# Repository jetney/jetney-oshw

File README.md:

# oshw
Open-source hardware design files from Jetney Development.

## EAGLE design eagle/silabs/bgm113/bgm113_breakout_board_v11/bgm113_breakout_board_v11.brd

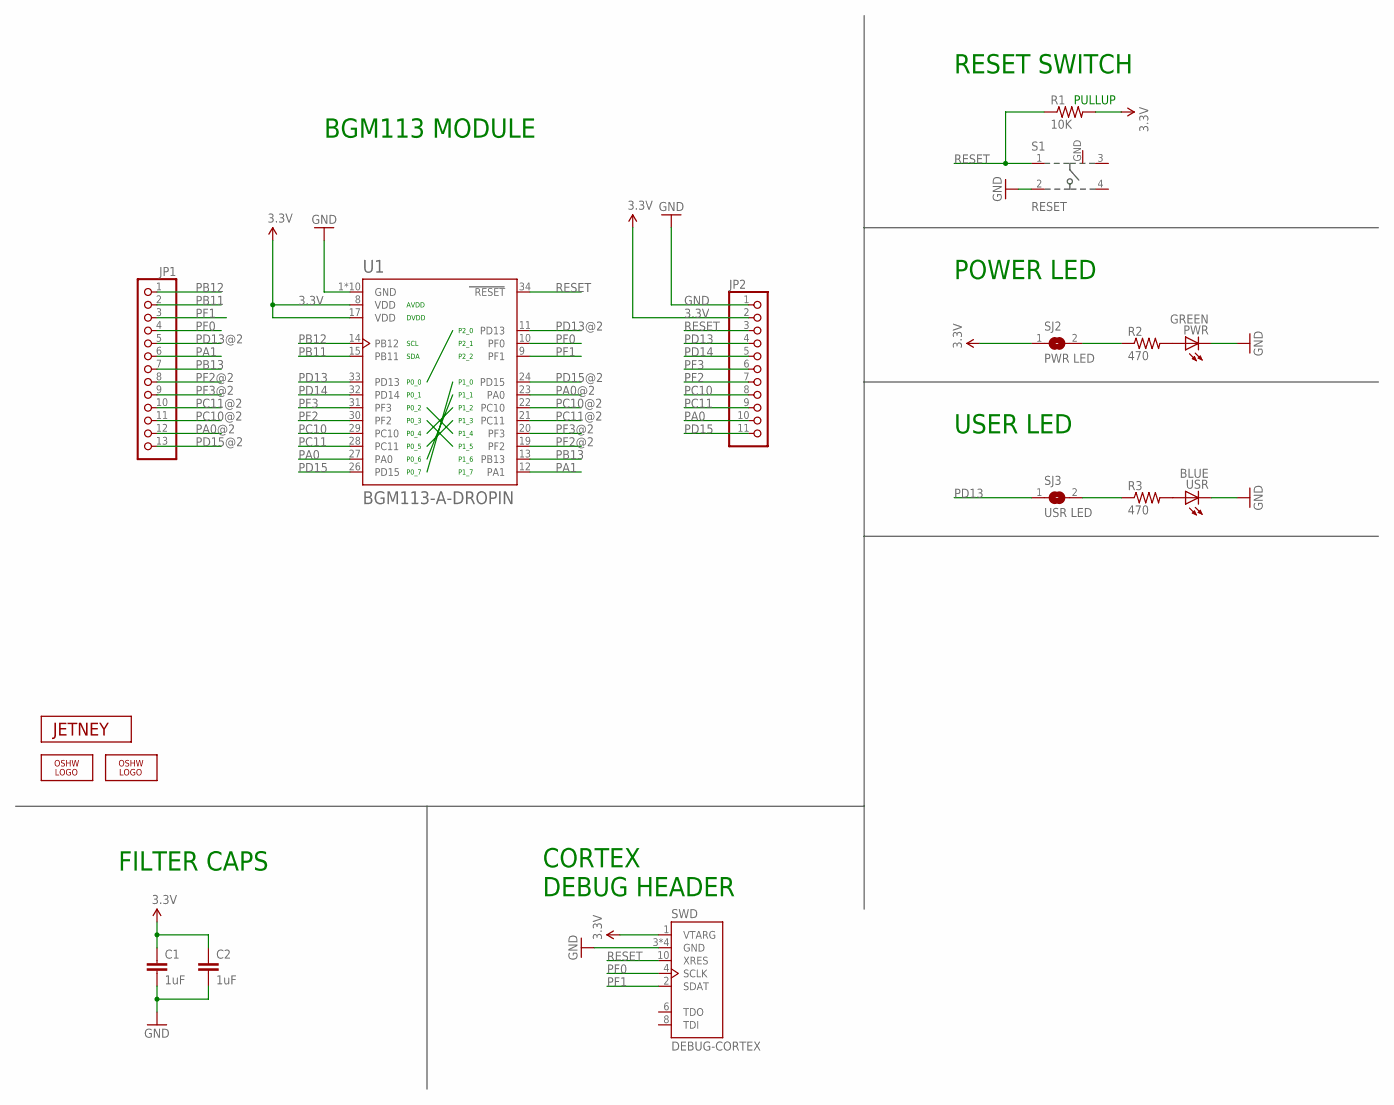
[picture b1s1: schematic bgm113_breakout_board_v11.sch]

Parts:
C1, C2: 1uF; 0603-CAP
JP1: PINHD-1X13; 1X13
JP2: PINHD-1X11; 1X11
LOGO1: OSHW_LOGO_FILLX0100-NT; OSHW_FILLX100_NOTEXT
LOGO2: OSHW_LOGO_FILLX0070-NT; OSHW_FILLX70_NOTEXT
PWR: GREEN; CHIPLED_0805
R1: 10K; 0603-RES
R2, R3: 470; R0603
S1: RESET; 101-IG
SJ2: PWR LED; SJ
SJ3: USR LED; SJ
SWD: DEBUG-CORTEX; DEBUG-50MIL
U1: BGM113-A-DROPIN; BLE113-A
U$2: JETNEY-LOGO-12
USR: BLUE; CHIPLED_0805

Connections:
3.3V: C1.1, C2.1, JP2.2, R1.2, SJ2.1, SWD.1 (VTARG), U1.8 (VDD), U1.17 (VDD)
GND: C1.2, C2.2, JP2.1, PWR.C, S1.2, S1.GND, SWD.3 (GND), SWD.5 (GND), SWD.7 (GND), SWD.9 (GND), U1.1 (GND), U1.2 (GND), U1.3 (GND), U1.4 (GND), U1.5 (GND), U1.6 (GND), U1.7 (GND), U1.18 (GND), U1.25 (GND), U1.36 (GND), USR.C
unnamed: PWR.A, R2.2
unnamed: R2.1, SJ2.2
unnamed: R3.2, USR.A
unnamed: R3.1, SJ3.2
PA0: JP2.10, U1.27 (PA0)
PA0@2: JP1.12, U1.23 (PA0)
PA1: JP1.6, U1.12 (PA1)
PB11: JP1.2, U1.15 (PB11)
PB12: JP1.1, U1.14 (PB12)
PB13: JP1.7, U1.13 (PB13)
PC10: JP2.8, U1.29 (PC10)
PC10@2: JP1.11, U1.22 (PC10)
PC11: JP2.9, U1.28 (PC11)
PC11@2: JP1.10, U1.21 (PC11)
PD13: JP2.4, SJ3.1, U1.33 (PD13)
PD13@2: JP1.5, U1.11 (PD13)
PD14: JP2.5, U1.32 (PD14)
PD15: JP2.11, U1.26 (PD15)
PD15@2: JP1.13, U1.24 (PD15)
PF0: JP1.4, SWD.4 (SCLK), U1.10 (PF0)
PF1: JP1.3, SWD.2 (SDAT), U1.9 (PF1)
PF2: JP2.7, U1.30 (PF2)
PF2@2: JP1.8, U1.19 (PF2)
PF3: JP2.6, U1.31 (PF3)
PF3@2: JP1.9, U1.20 (PF3)
RESET: JP2.3, R1.1, S1.1, SWD.10 (XRES), U1.34 (RESET)

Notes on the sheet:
POWER LED
USER LED
CORTEX DEBUG HEADER
BGM113 MODULE
RESET SWITCH
PULLUP
FILTER CAPS

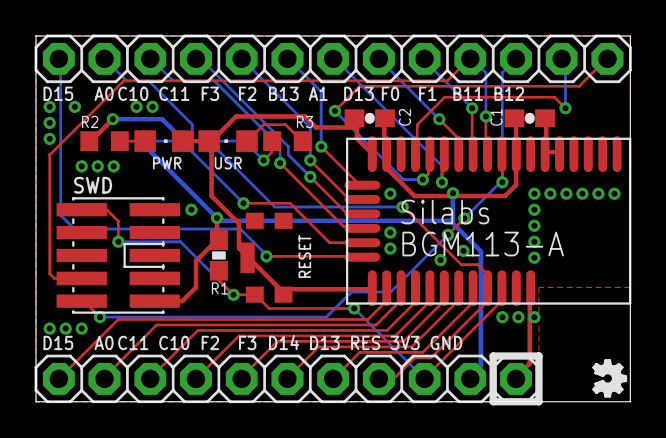
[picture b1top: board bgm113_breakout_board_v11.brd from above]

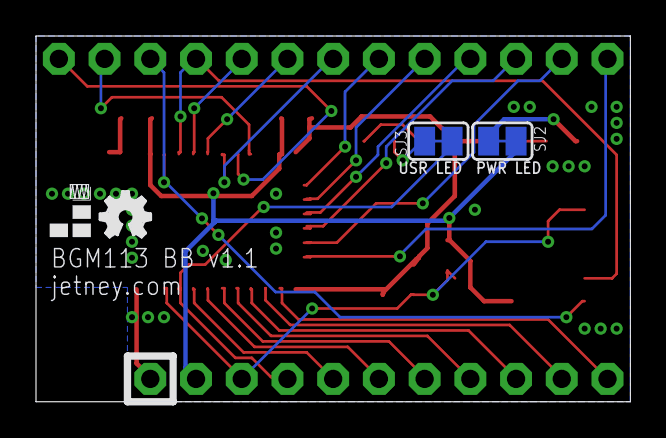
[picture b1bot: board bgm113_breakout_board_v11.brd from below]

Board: 2 copper layers, 33.0 x 20.3 mm, 17 parts (4 on the bottom side), 28 nets.

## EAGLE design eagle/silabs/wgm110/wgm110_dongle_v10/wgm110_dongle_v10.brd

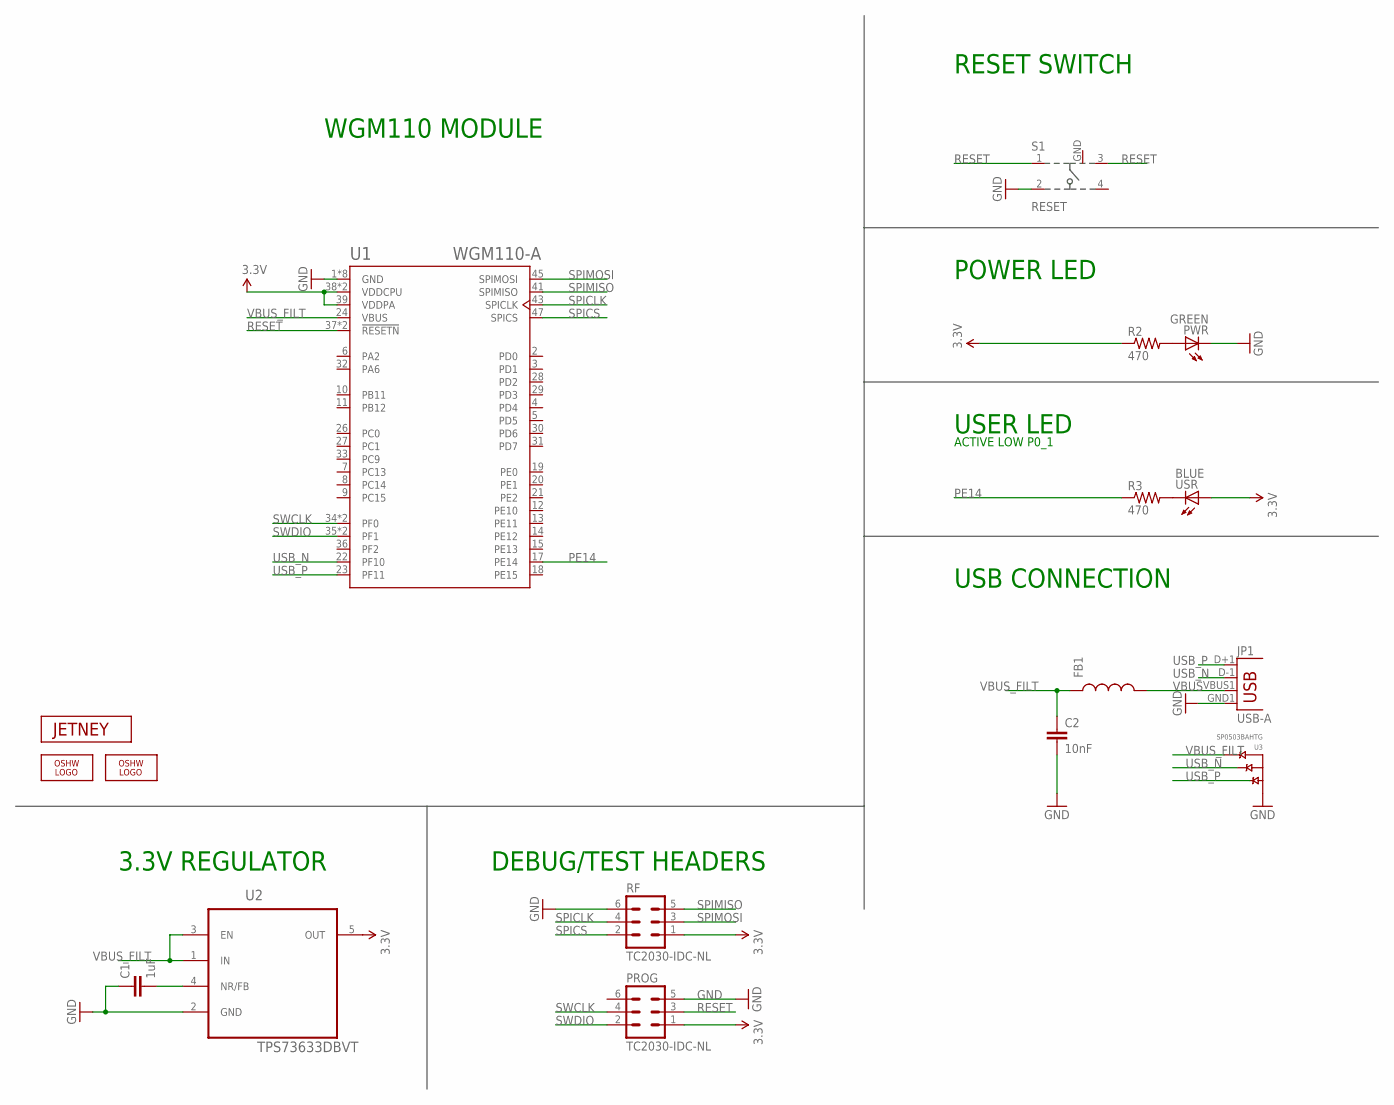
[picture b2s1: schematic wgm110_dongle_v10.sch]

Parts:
C1: 1uF; 0603-CAP
C2: 10nF; 0603-CAP
FB1: INDUCTOR0805; 0805
JP1: USB-A; USB-A-SMT-MALE-MOLEX
LOGO1: OSHW_LOGO_FILLX0100-NT; OSHW_FILLX100_NOTEXT
LOGO2: OSHW_LOGO_FILLX0070-NT; OSHW_FILLX70_NOTEXT
PROG: TC2030-IDC-NL
PWR: GREEN; CHIPLED_0805
R2, R3: 470; R0603
RF: TC2030-IDC-NL
S1: RESET; 101-IG
U1: WGM110-A
U2: TPS73633DBVT; SOT95P280X145-5N
U3: SP0503BAHTG; SOT143
U$2: JETNEY-LOGO-12
USR: BLUE; CHIPLED_0805

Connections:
3.3V: PROG.1, R2.1, RF.1, U1.38 (VDDCPU), U1.39 (VDDPA), U1.51 (VDDCPU), U2.5 (OUT), USR.A
GND: C1.1, C2.2, JP1.GND1 (GND), PROG.5, PWR.C, RF.6, S1.2, S1.GND, U1.1 (GND), U1.16 (GND), U1.25 (GND), U1.40 (GND), U1.42 (GND), U1.44 (GND), U1.46 (GND), U1.48 (GND), U2.2 (GND), U3.1 (GND)
PE14: R3.1, U1.17 (PE14)
PE14_LED: R3.2, USR.C
PWR_LED: PWR.A, R2.2
REG_BP: C1.2, U2.4 (NR/FB)
RESET: PROG.3, S1.1, S1.3, U1.37 (!RESETN), U1.49 (!RESETN)
SPICLK: RF.4, U1.43 (SPICLK)
SPICS: RF.2, U1.47 (SPICS)
SPIMISO: RF.5, U1.41 (SPIMISO)
SPIMOSI: RF.3, U1.45 (SPIMOSI)
SWCLK: PROG.4, U1.34 (PF0), U1.50 (PF0)
SWDIO: PROG.2, U1.35 (PF1), U1.52 (PF1)
USB_N: JP1.D-1 (D-), U1.22 (PF10), U3.3 (B)
USB_P: JP1.D+1 (D+), U1.23 (PF11), U3.2 (A)
VBUS: FB1.2, JP1.VBUS1 (VBUS)
VBUS_FILT: C2.1, FB1.1, U1.24 (VBUS), U2.1 (IN), U2.3 (EN), U3.4 (C)

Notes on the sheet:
POWER LED
USER LED
DEBUG/TEST HEADERS
WGM110 MODULE
RESET SWITCH
3.3V REGULATOR
ACTIVE LOW P0_1
USB CONNECTION

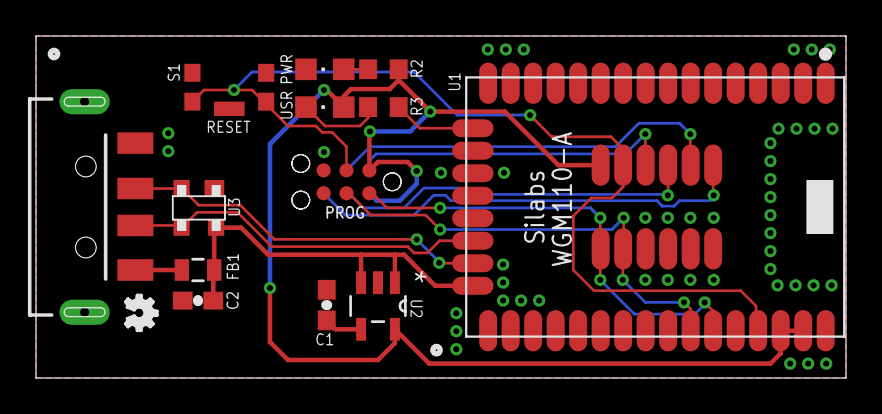
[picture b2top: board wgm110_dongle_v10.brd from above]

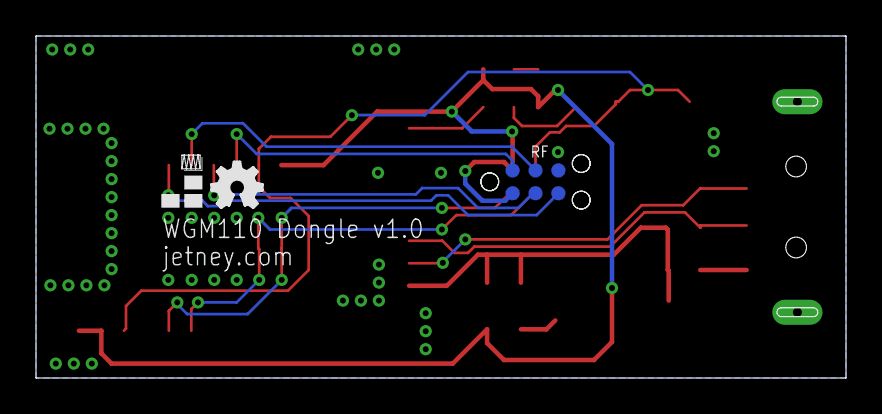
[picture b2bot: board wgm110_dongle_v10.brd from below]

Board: 2 copper layers, 45.0 x 19.0 mm, 17 parts (3 on the bottom side), 17 nets.

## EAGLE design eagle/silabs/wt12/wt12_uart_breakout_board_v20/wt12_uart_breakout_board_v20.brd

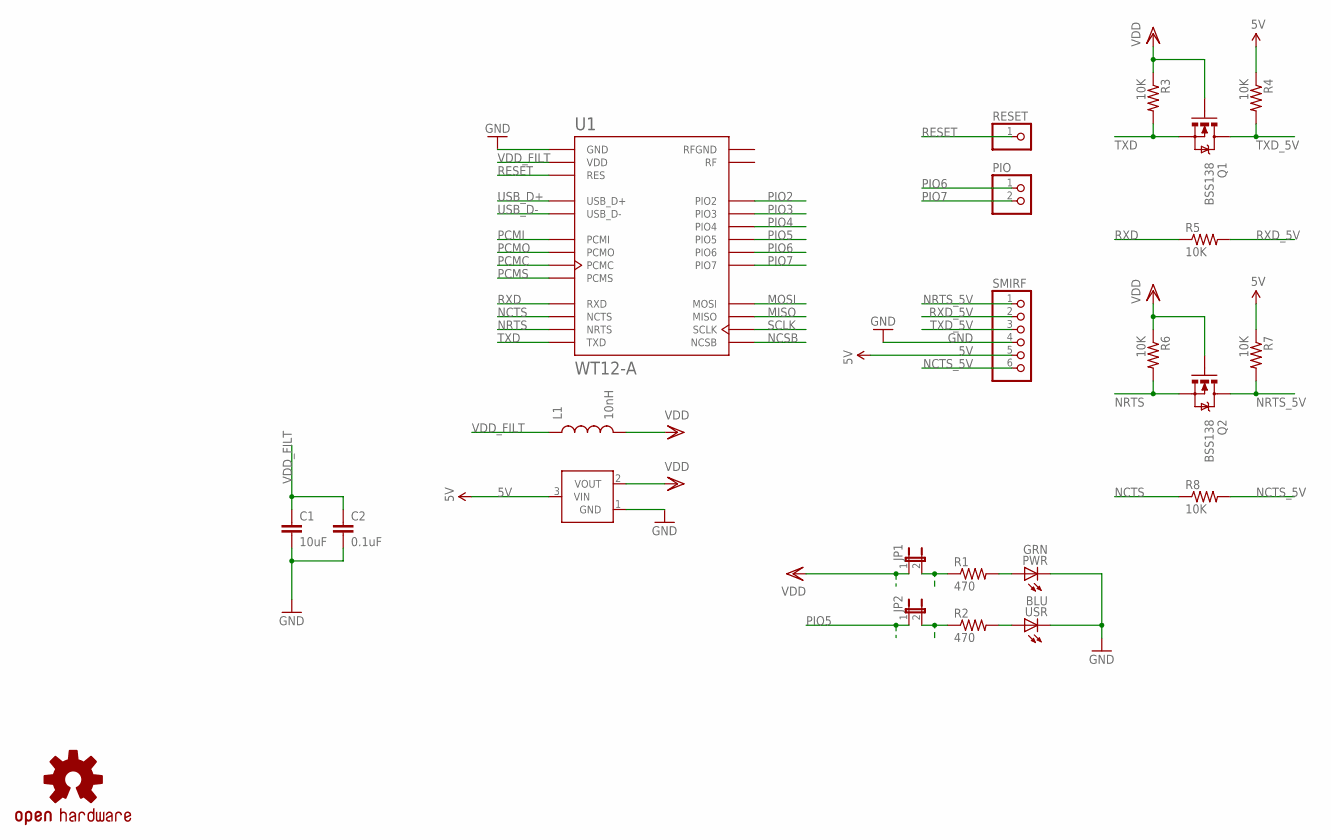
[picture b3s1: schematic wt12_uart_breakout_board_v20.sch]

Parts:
C1: 10uF; 0603-CAP
C2: 0.1uF; 0603-CAP
JP1, JP2: JUMPER-2SMD-NC; SJ_2S
L1: 10nH; 0603
PIO: PINHD-1X2; 1X02
PWR: GRN; CHIPLED_0805
Q1, Q2: BSS138; SOT23-3
R1, R2: 470; 0603-RES
R3, R4, R5, R6, R7, R8: 10K; 0603-RES
RESET: PINHD-1X1; 1X01
SMIRF: PINHD-1X6; 1X06
U1: WT12-A
U2: MCP1700; SOT23-3
U$5: OSHW-LOGOM; OSHW-LOGO-M
USR: BLU; CHIPLED_0805

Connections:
5V: R4.1, R7.1, SMIRF.5, U2.3 (VIN)
GND: C1.2, C2.2, PWR.C, SMIRF.4, U1.GND, U1.GND@2 (GND), U1.GND@3 (GND), U1.GND@4 (GND), U2.1 (GND), USR.C
MISO: U1.MISO
MOSI: U1.MOSI
unnamed: PWR.A, R1.2
unnamed: R2.2, USR.A
unnamed: JP2.2, R2.1
NCSB: U1.NCSB
NCTS: R8.1, U1.NCTS
NCTS_5V: R8.2, SMIRF.6
NRTS: Q2.2 (S), R6.2, U1.NRTS
NRTS_5V: Q2.3 (D), R7.2, SMIRF.1
PCMC: U1.PCMC
PCMI: U1.PCMI
PCMO: U1.PCMO
PCMS: U1.PCMS
PIO2: U1.PIO2
PIO3: U1.PIO3
PIO4: U1.PIO4
PIO5: JP2.1, U1.PIO5
PIO6: PIO.1, U1.PIO6
PIO7: PIO.2, U1.PIO7
RESET: RESET.1, U1.RES
RXD: R5.1, U1.RXD
RXD_5V: R5.2, SMIRF.2
SCLK: U1.SCLK
TXD: Q1.2 (S), R3.2, U1.TXD
TXD_5V: Q1.3 (D), R4.2, SMIRF.3
USB_D+: U1.USB_D+
USB_D-: U1.USB_D-
VDD: JP1.1, L1.2, Q1.1 (G), Q2.1 (G), R3.1, R6.1, U2.2 (VOUT)
VDDJP1: JP1.2, R1.1
VDD_FILT: C1.1, C2.1, L1.1, U1.VDD, U1.VDD@2 (VDD)

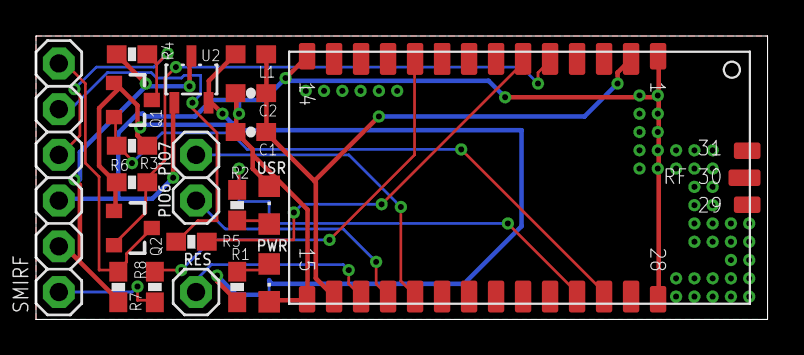
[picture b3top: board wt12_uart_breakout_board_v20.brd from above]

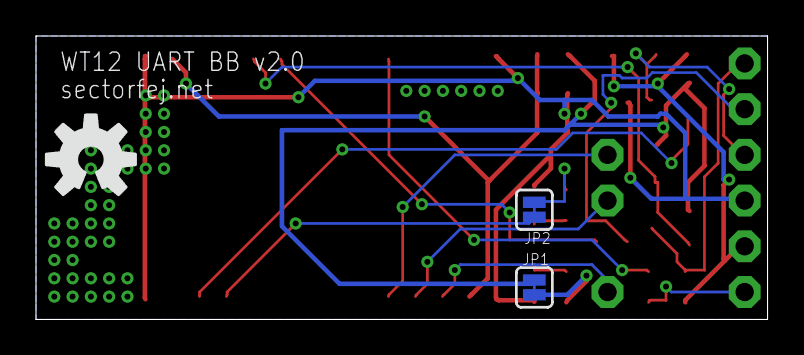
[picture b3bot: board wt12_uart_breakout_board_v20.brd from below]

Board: 2 copper layers, 40.6 x 15.7 mm, 23 parts (3 on the bottom side), 20 nets.

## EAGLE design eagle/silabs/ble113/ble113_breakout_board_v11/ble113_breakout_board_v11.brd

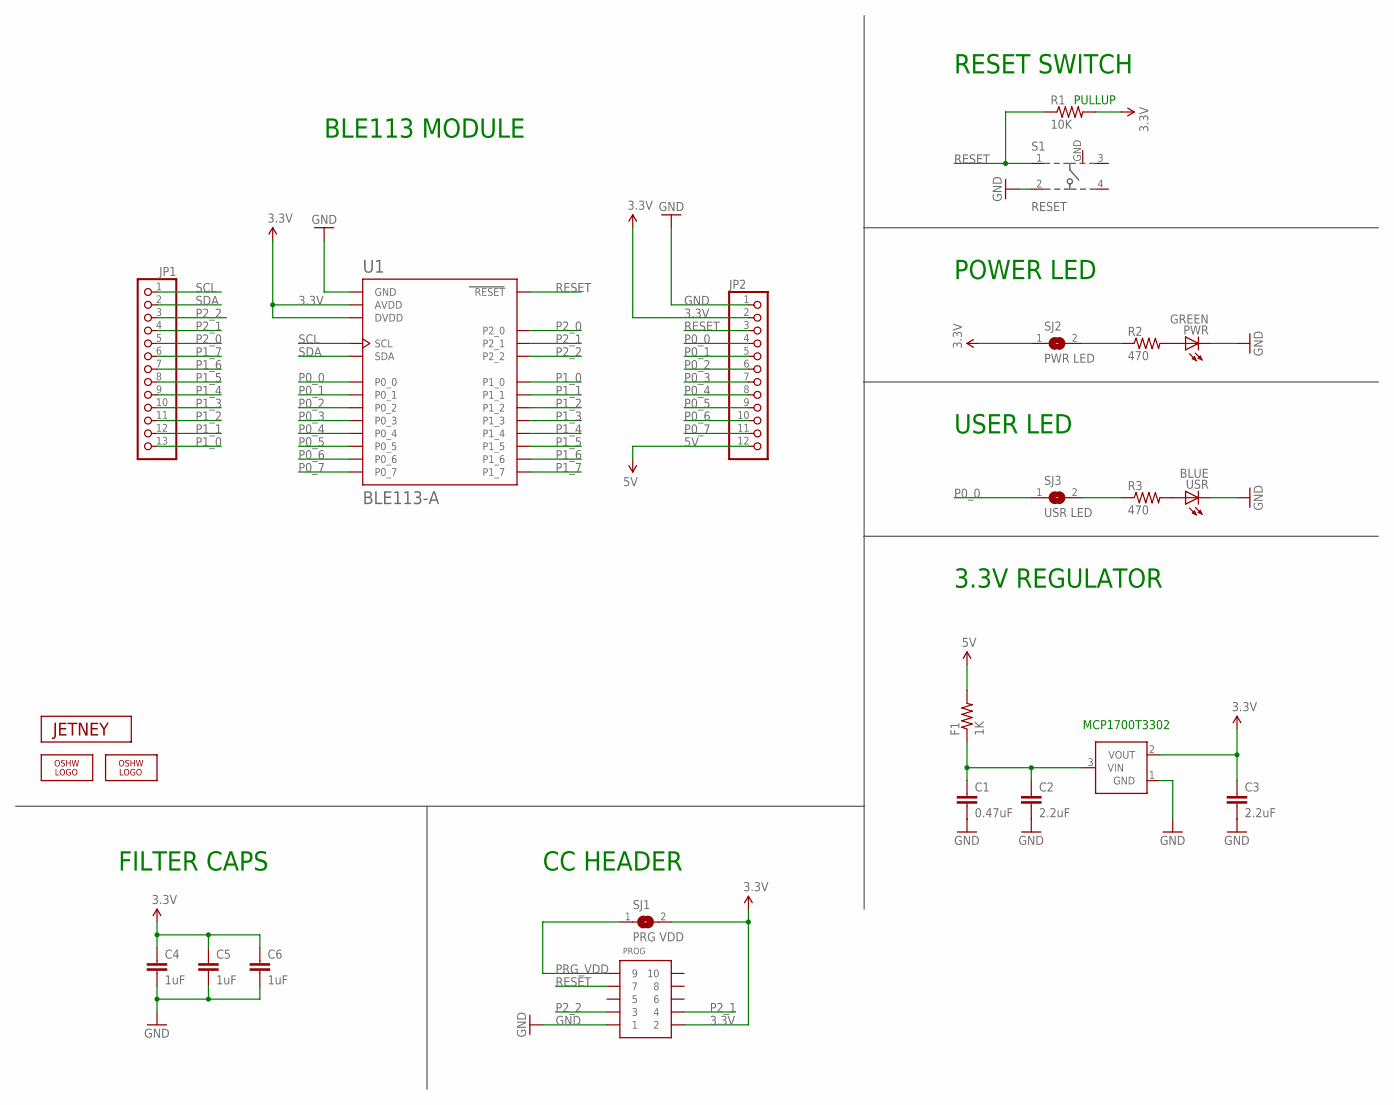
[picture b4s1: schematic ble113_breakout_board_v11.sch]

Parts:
C1: 0.47uF; 0603-CAP
C2, C3: 2.2uF; 0603-CAP
C4, C5, C6: 1uF; 0603-CAP
F1: 1K; 0805
JP1: PINHD-1X13; 1X13
JP2: PINHD-1X12; 1X12
LOGO1: OSHW_LOGO_FILLX0100-NT; OSHW_FILLX100_NOTEXT
LOGO2: OSHW_LOGO_FILLX0070-NT; OSHW_FILLX70_NOTEXT
PROG: CONN_5-2-FTSH-V; FTSH-105-DV
PWR: GREEN; CHIPLED_0805
R1: 10K; 0603-RES
R2, R3: 470; R0603
S1: RESET; 101-IG
SJ1: PRG VDD; SJ
SJ2: PWR LED; SJ
SJ3: USR LED; SJ
U1: BLE113-A
U2: MCP1700; SOT23-3
U$2: JETNEY-LOGO-12
USR: BLUE; CHIPLED_0805

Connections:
3.3V: C3.1, C4.1, C5.1, C6.1, JP2.2, PROG.2, R1.2, SJ1.2, SJ2.1, U1.AVDD, U1.DVDD, U2.2 (VOUT)
5V: F1.2, JP2.12
5VF: C1.1, C2.1, F1.1, U2.3 (VIN)
GND: C1.2, C2.2, C3.2, C4.2, C5.2, C6.2, JP2.1, PROG.1, PWR.C, S1.2, S1.GND, U1.GND, U1.GND@2 (GND), U1.GND@3 (GND), U1.GND@4 (GND), U1.GND@5 (GND), U1.GND@6 (GND), U1.GND@7 (GND), U1.GND@8 (GND), U1.GND@9 (GND), U1.GND@10 (GND), U2.1 (GND), USR.C
unnamed: PWR.A, R2.2
unnamed: R2.1, SJ2.2
unnamed: R3.2, USR.A
unnamed: R3.1, SJ3.2
P0_0: JP2.4, SJ3.1, U1.P0_0
P0_1: JP2.5, U1.P0_1
P0_2: JP2.6, U1.P0_2
P0_3: JP2.7, U1.P0_3
P0_4: JP2.8, U1.P0_4
P0_5: JP2.9, U1.P0_5
P0_6: JP2.10, U1.P0_6
P0_7: JP2.11, U1.P0_7
P1_0: JP1.13, U1.P1_0
P1_1: JP1.12, U1.P1_1
P1_2: JP1.11, U1.P1_2
P1_3: JP1.10, U1.P1_3
P1_4: JP1.9, U1.P1_4
P1_5: JP1.8, U1.P1_5
P1_6: JP1.7, U1.P1_6
P1_7: JP1.6, U1.P1_7
P2_0: JP1.5, U1.P2_0
P2_1: JP1.4, PROG.4, U1.P2_1
P2_2: JP1.3, PROG.3, U1.P2_2
PRG_VDD: PROG.9, SJ1.1
RESET: JP2.3, PROG.7, R1.1, S1.1, U1.RESET
SCL: JP1.1, U1.SCL
SDA: JP1.2, U1.SDA

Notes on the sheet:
POWER LED
USER LED
CC HEADER
BLE113 MODULE
3.3V REGULATOR
RESET SWITCH
PULLUP
MCP1700T3302
FILTER CAPS

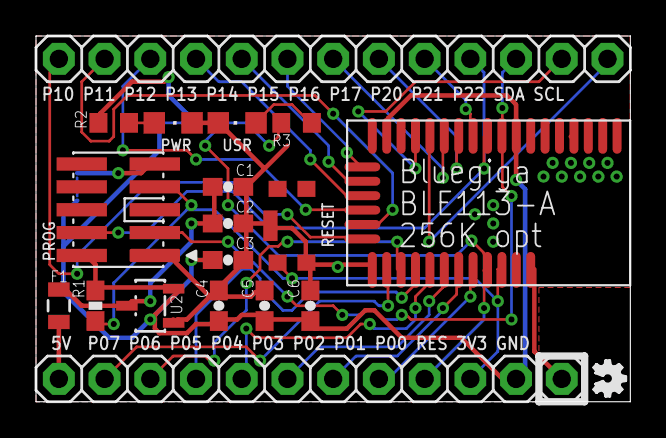
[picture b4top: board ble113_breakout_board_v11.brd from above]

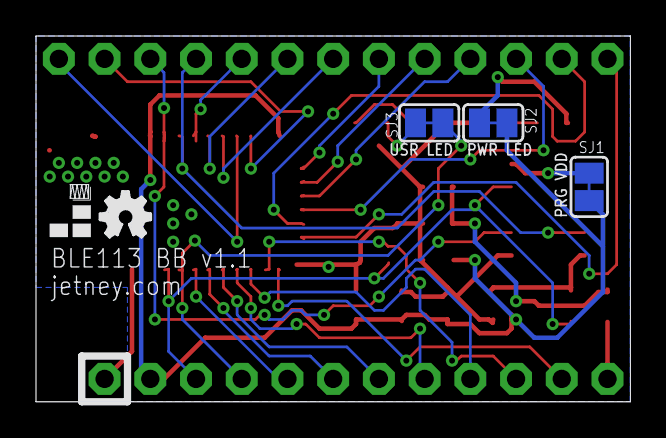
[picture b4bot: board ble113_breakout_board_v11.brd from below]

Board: 2 copper layers, 33.0 x 20.3 mm, 24 parts (5 on the bottom side), 31 nets.

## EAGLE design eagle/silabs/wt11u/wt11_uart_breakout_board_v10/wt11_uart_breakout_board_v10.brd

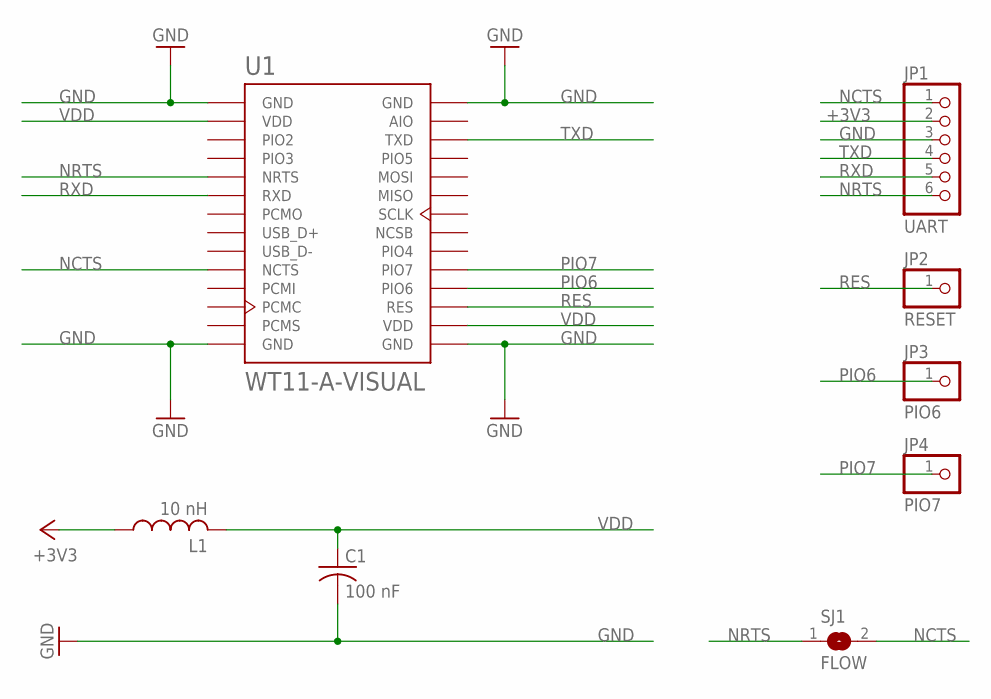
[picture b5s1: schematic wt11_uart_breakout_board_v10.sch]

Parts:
C1: 100 nF; C0603K
JP1: UART; 1X06
JP2: RESET; 1X01
JP3: PIO6; 1X01
JP4: PIO7; 1X01
L1: 10 nH; L2012C
SJ1: FLOW; SJ
U1: WT11-A-VISUAL; WT11-A

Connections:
+3V3: JP1.2, L1.1
GND: C1.2, JP1.3, U1.GND1 (GND), U1.GND2 (GND), U1.GND3 (GND), U1.GND4 (GND)
NCTS: JP1.1, SJ1.2, U1.NCTS
NRTS: JP1.6, SJ1.1, U1.NRTS
PIO6: JP3.1, U1.PIO6
PIO7: JP4.1, U1.PIO7
RES: JP2.1, U1.RES
RXD: JP1.5, U1.RXD
TXD: JP1.4, U1.TXD
VDD: C1.1, L1.2, U1.VDD1 (VDD), U1.VDD2 (VDD)

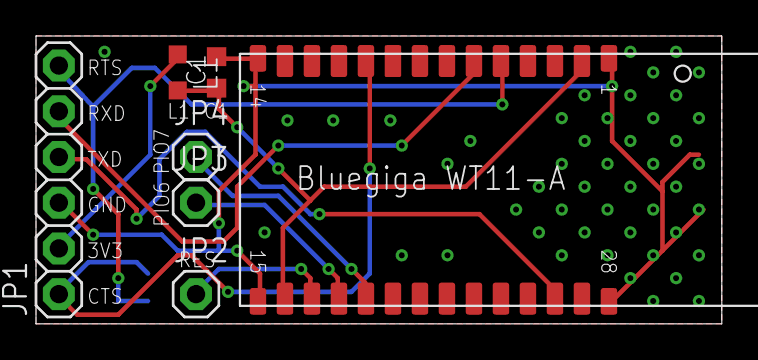
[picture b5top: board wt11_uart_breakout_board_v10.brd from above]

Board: 2 copper layers, 38.1 x 16.0 mm, 8 parts (1 on the bottom side), 10 nets.

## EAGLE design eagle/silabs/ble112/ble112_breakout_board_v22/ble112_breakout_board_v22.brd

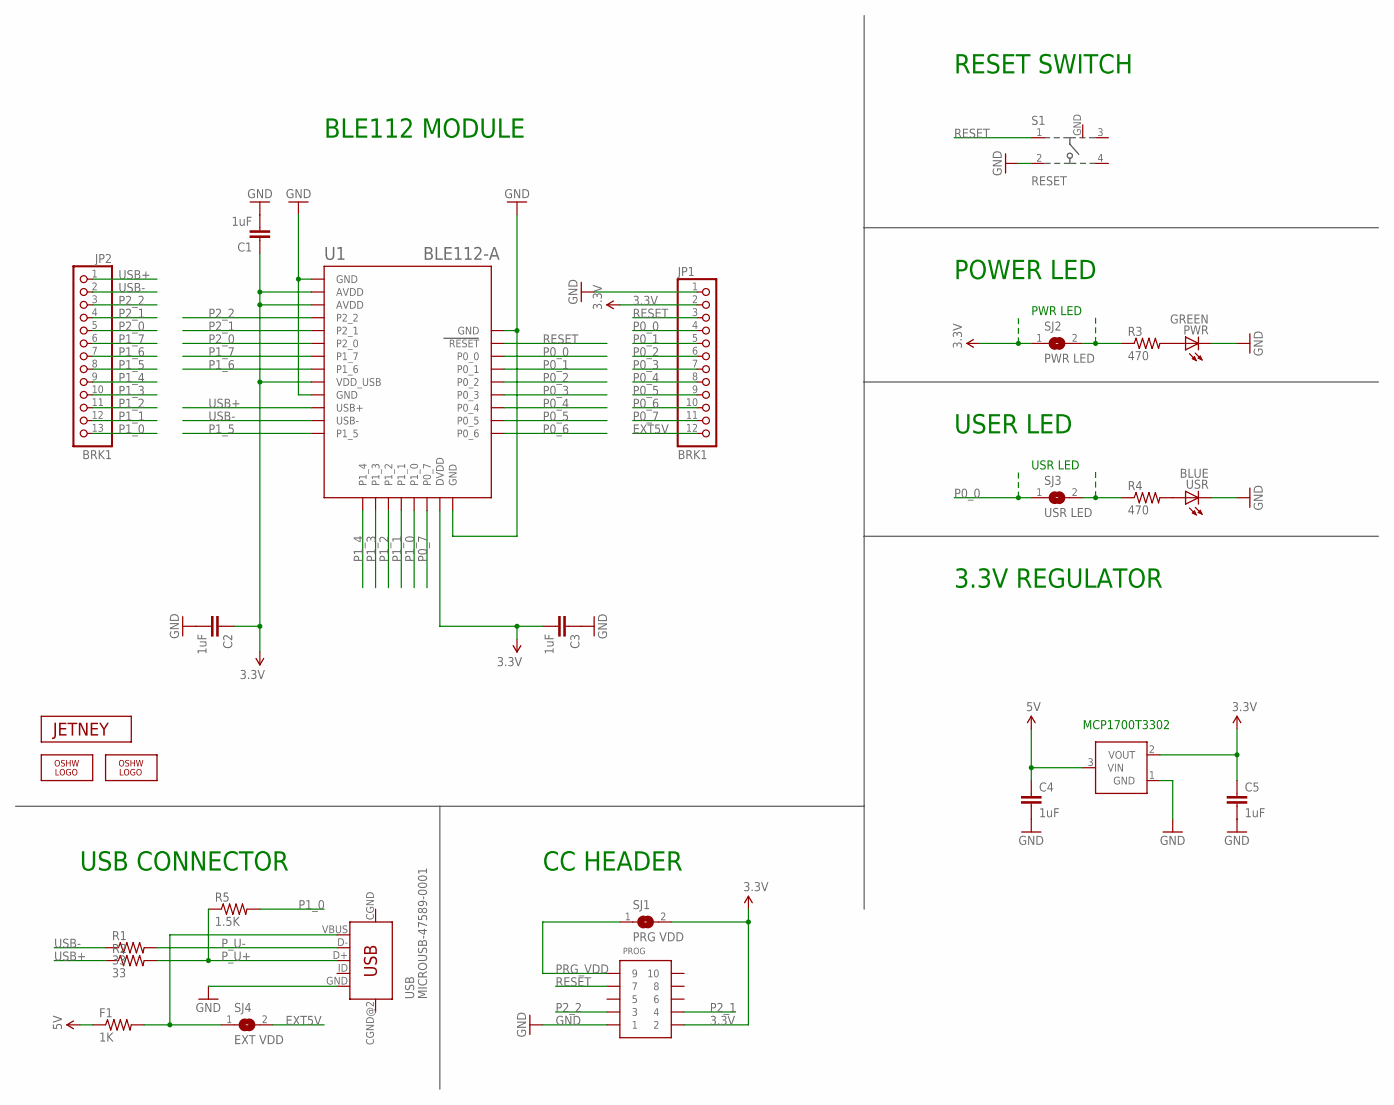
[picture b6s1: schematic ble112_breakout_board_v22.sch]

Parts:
C1, C2, C3, C4, C5: 1uF; 0603-CAP
F1: 1K; 0805
JP1: BRK1; 1X12
JP2: BRK1; 1X13
LOGO1, LOGO2: OSHW_LOGO_FILLX0100-NT; OSHW_FILLX100_NOTEXT
PROG: CONN_5-2-FTSH-V; FTSH-105-DV
PWR: GREEN; CHIPLED_0805
R1, R2: 33; 0603-RES
R3, R4: 470; R0603
R5: 1.5K; 0603-RES
S1: RESET; 101-IG
SJ1: PRG VDD; SJ
SJ2: PWR LED; SJ
SJ3: USR LED; SJ
SJ4: EXT VDD; SJ
U1: BLE112-A
U2: MCP1700; SOT23-3
U$3: JETNEY-LOGO-12
USB: MICROUSB-47589-0001
USR: BLUE; CHIPLED_0805

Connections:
3.3V: C1.1, C2.1, C3.2, C5.1, JP1.2, PROG.2, SJ1.2, SJ2.1, U1.AVDD, U1.AVDD@2 (AVDD), U1.DVDD, U1.VDD_USB, U2.2 (VOUT)
5V: C4.1, F1.1, U2.3 (VIN)
EXT5V: JP1.12, SJ4.2
GND: C1.2, C2.2, C3.1, C4.2, C5.2, JP1.1, PROG.1, PWR.C, S1.2, S1.GND, U1.GND, U1.GND@2 (GND), U1.GND@3 (GND), U1.GND@4 (GND), U2.1 (GND), USB.GND, USR.C
unnamed: PWR.A, R3.2
unnamed: R3.1, SJ2.2
unnamed: R4.2, USR.A
unnamed: R4.1, SJ3.2
P0_0: JP1.4, SJ3.1, U1.P0_0
P0_1: JP1.5, U1.P0_1
P0_2: JP1.6, U1.P0_2
P0_3: JP1.7, U1.P0_3
P0_4: JP1.8, U1.P0_4
P0_5: JP1.9, U1.P0_5
P0_6: JP1.10, U1.P0_6
P0_7: JP1.11, U1.P0_7
P1_0: JP2.13, R5.2, U1.P1_0
P1_1: JP2.12, U1.P1_1
P1_2: JP2.11, U1.P1_2
P1_3: JP2.10, U1.P1_3
P1_4: JP2.9, U1.P1_4
P1_5: JP2.8, U1.P1_5
P1_6: JP2.7, U1.P1_6
P1_7: JP2.6, U1.P1_7
P2_0: JP2.5, U1.P2_0
P2_1: JP2.4, PROG.4, U1.P2_1
P2_2: JP2.3, PROG.3, U1.P2_2
PRG_VDD: PROG.9, SJ1.1
P_U+: R2.2, R5.1, USB.D+
P_U-: R1.2, USB.D-
RESET: JP1.3, PROG.7, S1.1, U1.RESET
USB+: JP2.1, R2.1, U1.USB+
USB-: JP2.2, R1.1, U1.USB-
VBUS: F1.2, SJ4.1, USB.VBUS

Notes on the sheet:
PWR LED
USR LED
POWER LED
USER LED
USB CONNECTOR
CC HEADER
BLE112 MODULE
3.3V REGULATOR
RESET SWITCH
MCP1700T3302

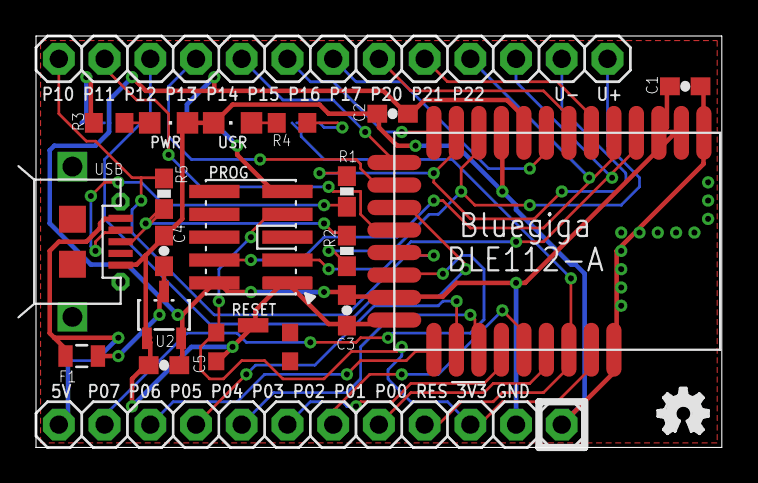
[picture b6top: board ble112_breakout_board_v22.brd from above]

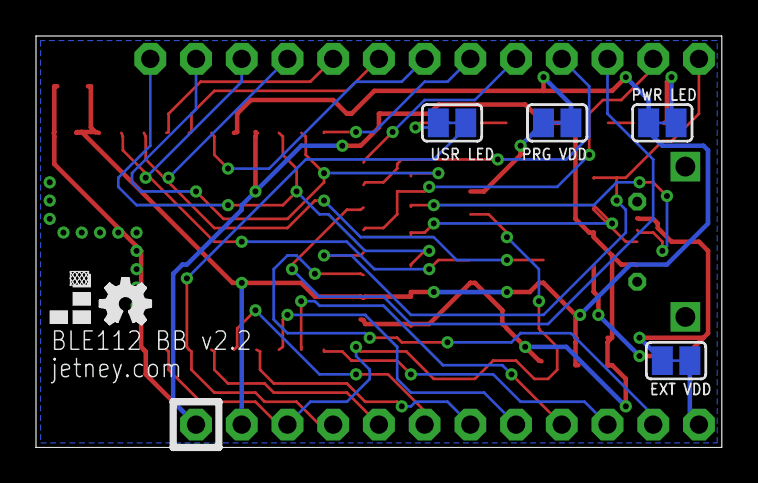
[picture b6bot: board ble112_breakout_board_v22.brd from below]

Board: 2 copper layers, 38.1 x 22.9 mm, 27 parts (6 on the bottom side), 34 nets.

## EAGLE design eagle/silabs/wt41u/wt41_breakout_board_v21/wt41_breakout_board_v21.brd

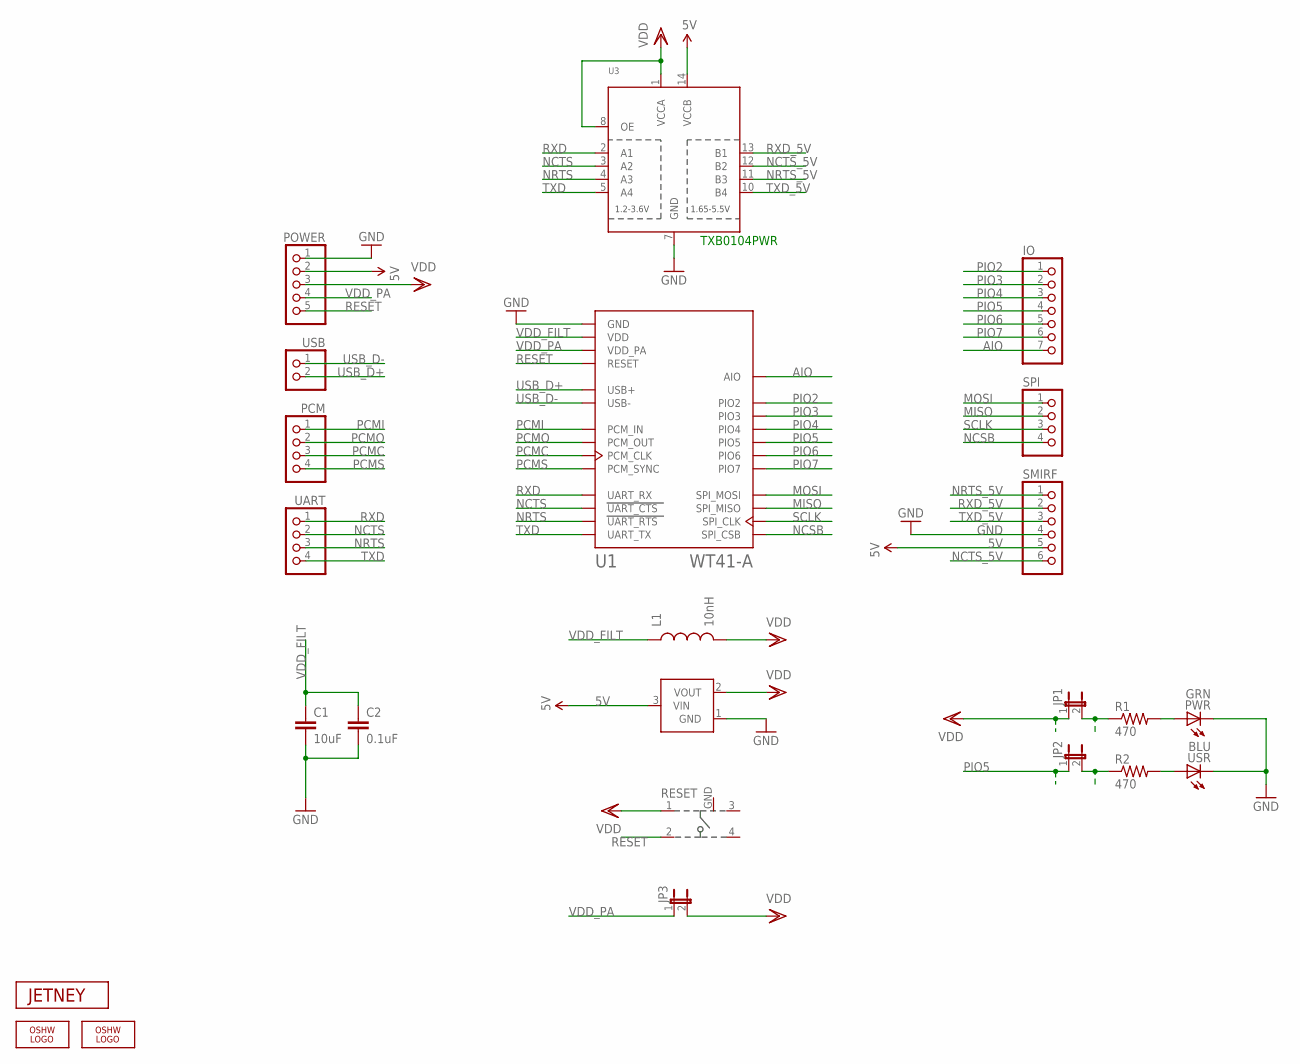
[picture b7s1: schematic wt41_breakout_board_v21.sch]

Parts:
C1: 10uF; 0603-CAP
C2: 0.1uF; 0603-CAP
IO: PINHD-1X7; 1X07
JP1, JP2, JP3: JUMPER-2SMD-NC; SJ_2S
L1: 10nH; 0603
LOGO1, LOGO2: OSHW_LOGO_FILLX0070-NT; OSHW_FILLX70_NOTEXT
PCM: PINHD-1X4; 1X04
POWER: PINHD-1X5; 1X05
PWR: GRN; CHIPLED_0805
R1, R2: 470; 0603-RES
RESET: 101-IG
SMIRF: PINHD-1X6; 1X06
SPI: PINHD-1X4; 1X04
U1: WT41-A
U2: MCP1700; SOT23-3
U3: TXB0104PWR; TSSOP14
U$2: JETNEY-LOGO-12
UART: PINHD-1X4; 1X04
USB: PINHD-1X2; 1X02
USR: BLU; CHIPLED_0805

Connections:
5V: POWER.2, SMIRF.5, U2.3 (VIN), U3.14 (VCCB)
AIO: IO.7, U1.AIO
GND: C1.2, C2.2, POWER.1, PWR.C, RESET.GND, SMIRF.4, U1.GND, U1.GND@2 (GND), U1.GND@3 (GND), U1.GND@4 (GND), U1.GND@5 (GND), U1.GND@6 (GND), U1.GND@7 (GND), U1.GND@8 (GND), U1.GND@9 (GND), U1.GND@10 (GND), U1.GND@11 (GND), U1.GND@12 (GND), U1.GND@13 (GND), U1.GND@14 (GND), U1.GND@15 (GND), U1.GND@16 (GND), U1.GND@17 (GND), U1.GND@18 (GND), U1.GND@19 (GND), U1.GND@20 (GND), U1.GND@21 (GND), U1.GND@22 (GND), U1.GND@23 (GND), U1.GND@24 (GND), U1.GND@25 (GND), U1.GND@26 (GND), U1.GND@27 (GND), U1.GND@28 (GND), U1.GND@29 (GND), U1.GND@30 (GND), U1.GND@31 (GND), U2.1 (GND), U3.7 (GND), USR.C
MISO: SPI.2, U1.SPI_MISO
MOSI: SPI.1, U1.SPI_MOSI
unnamed: PWR.A, R1.2
unnamed: R2.2, USR.A
unnamed: JP2.2, R2.1
NCSB: SPI.4, U1.SPI_CSB
NCTS: U1.UART_CTS, U3.3 (A2), UART.2
NCTS_5V: SMIRF.6, U3.12 (B2)
NRTS: U1.UART_RTS, U3.4 (A3), UART.3
NRTS_5V: SMIRF.1, U3.11 (B3)
PCMC: PCM.3, U1.PCM_CLK
PCMI: PCM.1, U1.PCM_IN
PCMO: PCM.2, U1.PCM_OUT
PCMS: PCM.4, U1.PCM_SYNC
PIO2: IO.1, U1.PIO2
PIO3: IO.2, U1.PIO3
PIO4: IO.3, U1.PIO4
PIO5: IO.4, JP2.1, U1.PIO5
PIO6: IO.5, U1.PIO6
PIO7: IO.6, U1.PIO7
RESET: POWER.5, RESET.2, U1.RESET
RXD: U1.UART_RX, U3.2 (A1), UART.1
RXD_5V: SMIRF.2, U3.13 (B1)
SCLK: SPI.3, U1.SPI_CLK
TXD: U1.UART_TX, U3.5 (A4), UART.4
TXD_5V: SMIRF.3, U3.10 (B4)
USB_D+: U1.USB+, USB.2
USB_D-: U1.USB-, USB.1
VDD: JP1.1, JP3.2, L1.2, POWER.3, RESET.1, U2.2 (VOUT), U3.1 (VCCA), U3.8 (OE)
VDDJP1: JP1.2, R1.1
VDD_FILT: C1.1, C2.1, L1.1, U1.VDD
VDD_PA: JP3.1, POWER.4, U1.VDD_PA

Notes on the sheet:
TXB0104PWR

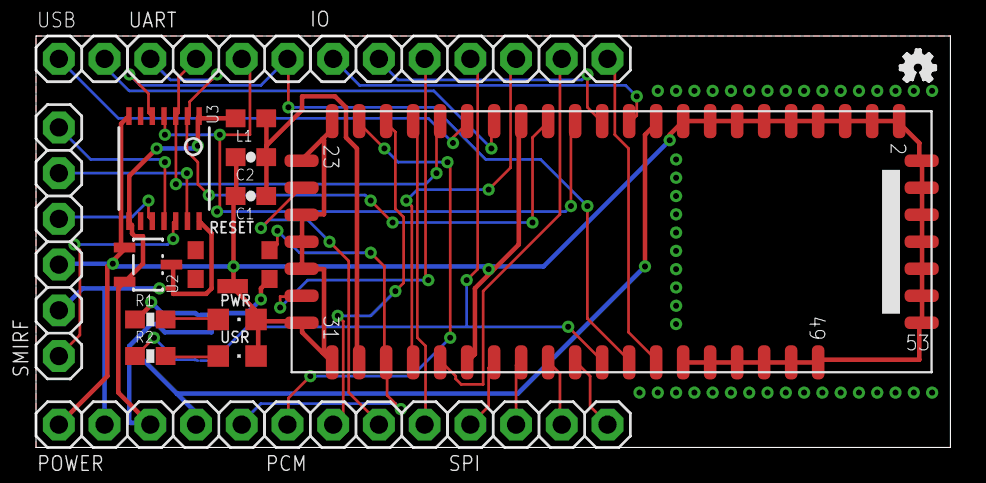
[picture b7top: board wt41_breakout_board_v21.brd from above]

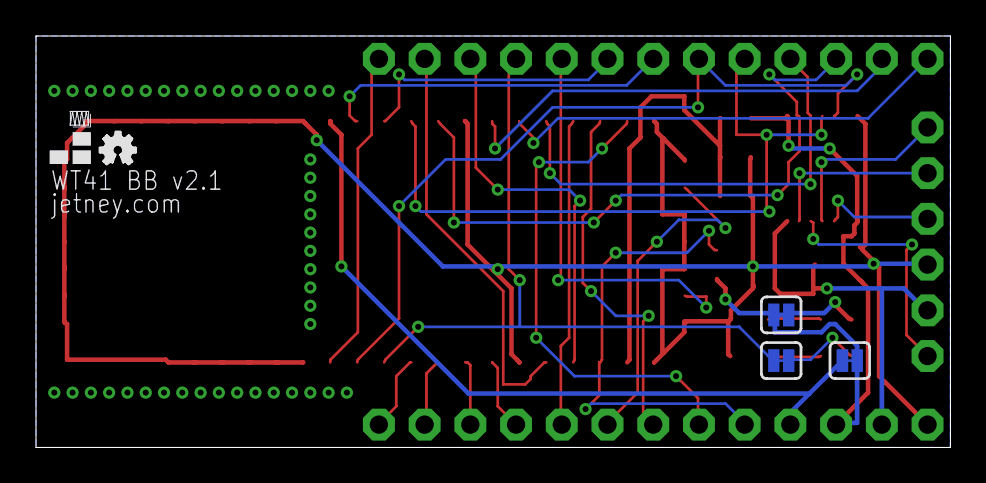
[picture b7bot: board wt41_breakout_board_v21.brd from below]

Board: 2 copper layers, 50.8 x 22.9 mm, 24 parts (5 on the bottom side), 35 nets.

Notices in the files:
parts and their libraries:
SparkFun: Licensing: CC v3.0 Share-Alike You are welcome to use this library for commercial purposes.
jetney-silabs-modules: Package design from "pretty-eagle-libs" at https://github.com/esden/pretty-eagle-libs/blob/master/pel_misc.lbr by @esden at Github. (CC-BY-SA-3.0)
